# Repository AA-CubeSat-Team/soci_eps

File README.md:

# soci_eps

This is a repo for the EPS (electrical power system) subsystem of SOC-I.

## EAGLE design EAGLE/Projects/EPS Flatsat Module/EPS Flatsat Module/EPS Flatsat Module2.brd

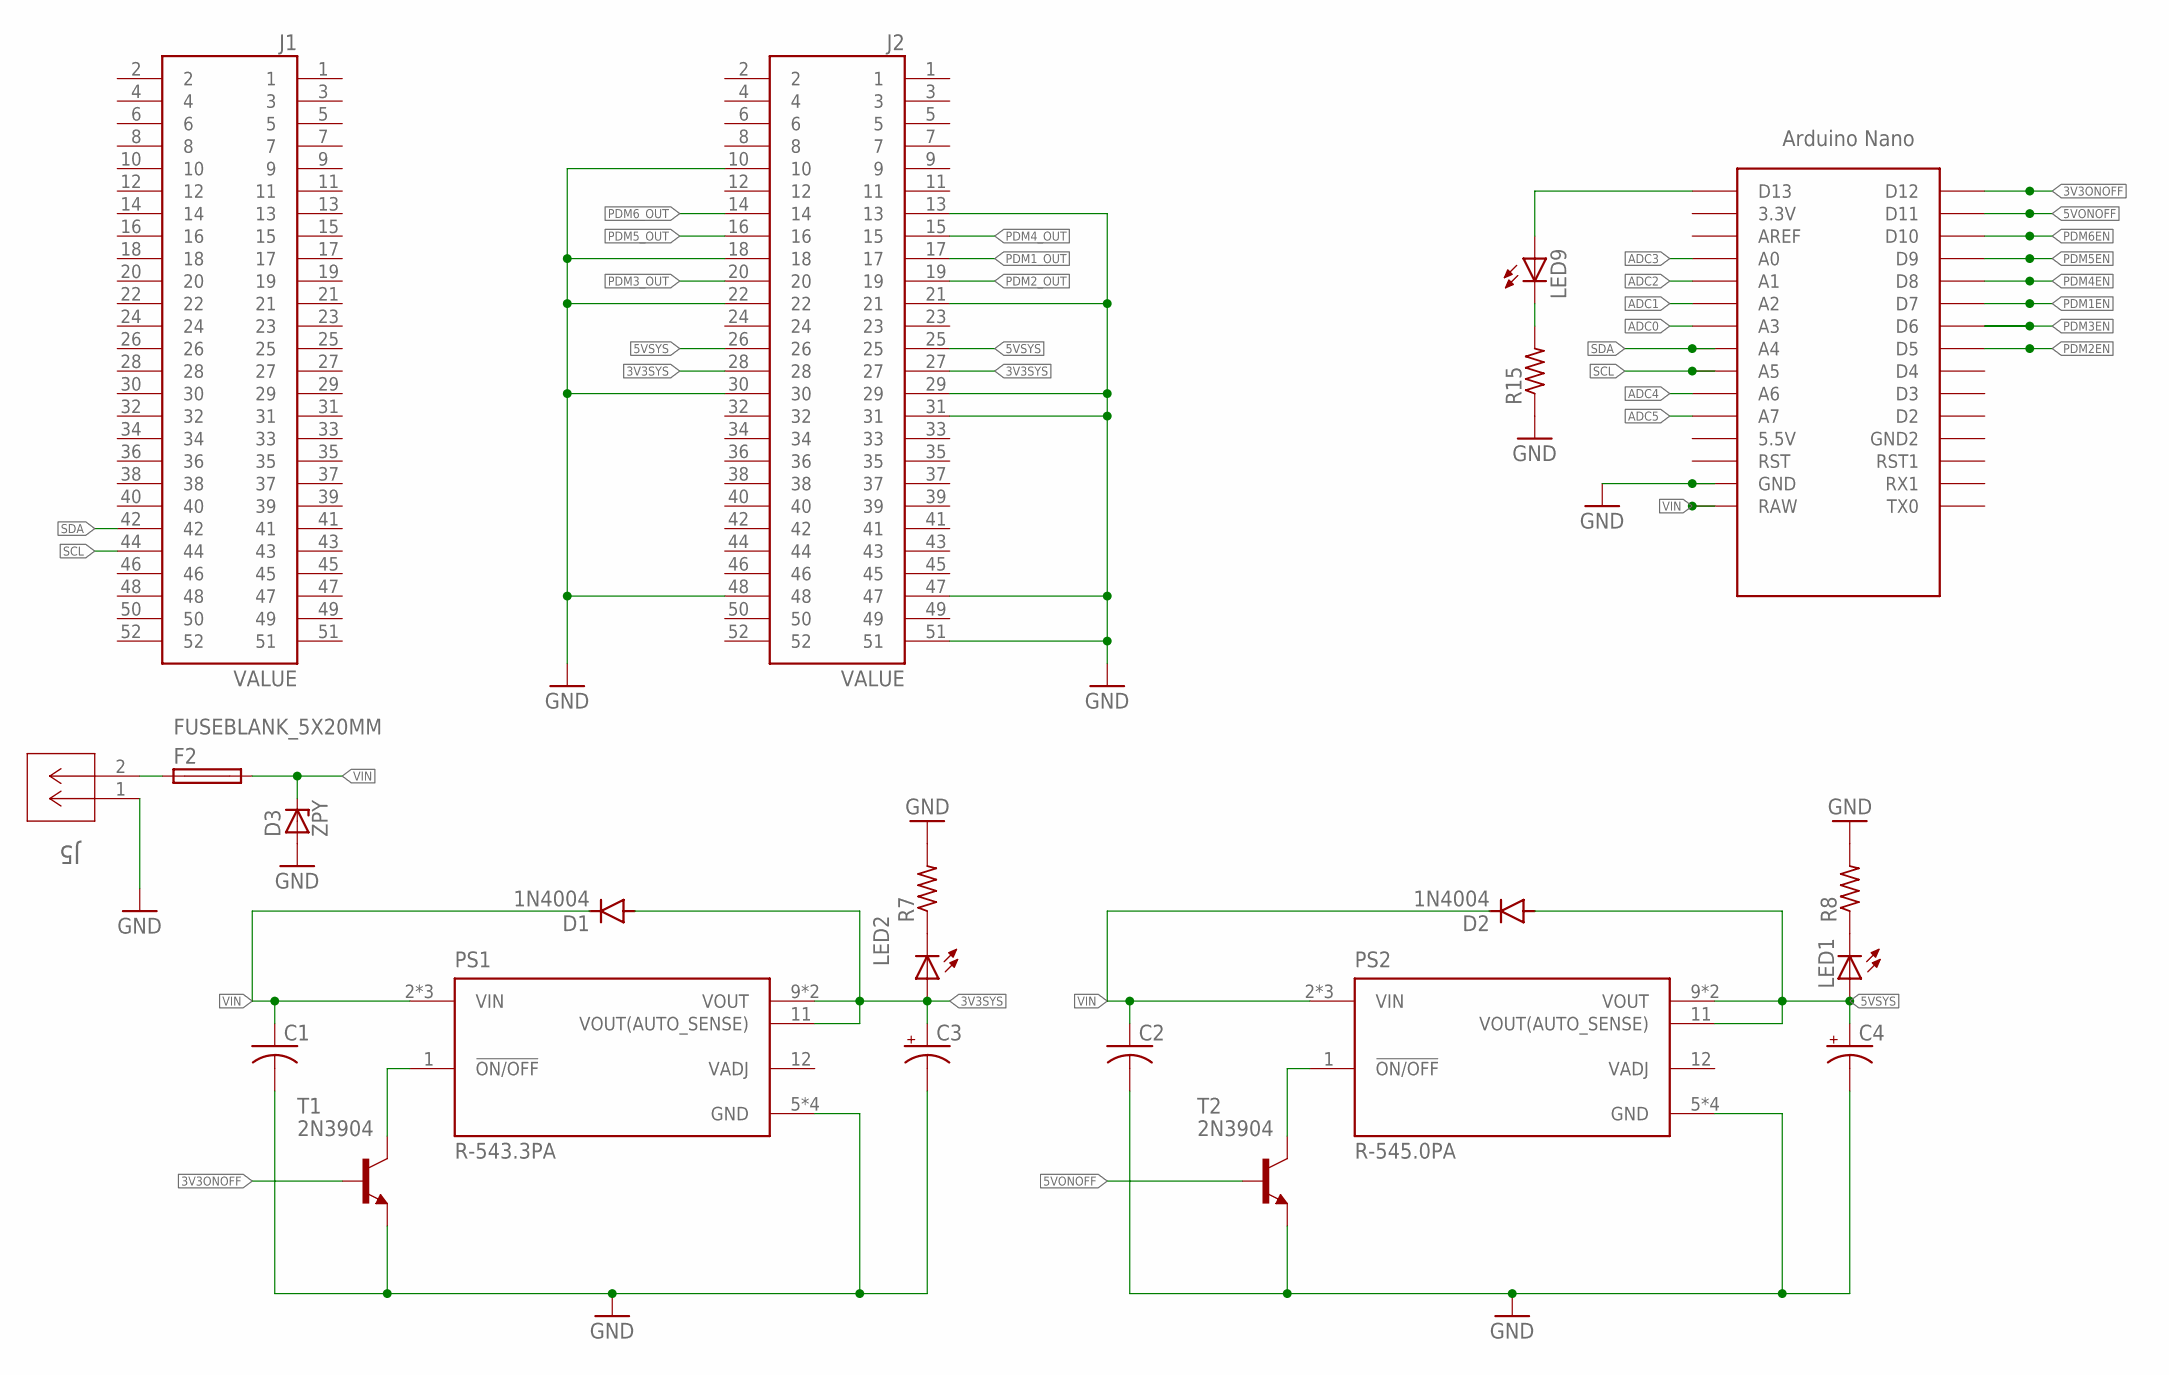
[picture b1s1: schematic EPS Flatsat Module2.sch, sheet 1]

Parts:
C1, C2: C-USC0805; C0805
C3, C4: CPOL-USE2.5-6; E2,5-6
D1, D2: 1N4004; DO41-10
D3: ZPY; DO41Z10
F2: FUSEBLANK_5X20MM; FUSE_HOLDER_5X20MM
J1, J2: ESQ-126-39-G-D; SAMTEC_ESQ-126-39-G-D
J5: 1985881; CONN_1715022_PXC
LED1, LED2: LEDCHIPLED_0805; CHIPLED_0805
LED9: LEDCHIP-LED0805; CHIP-LED0805
PS1: R-543.3PA; CONV_R-543.3PA
PS2: R-545.0PA; CONV_R-545.0PA
R7, R8, R15: R-US_R0805; R0805
T1, T2: 2N3904; TO92
U$1: NANO

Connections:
3V3ONOFF: T1.2 (B), U$1.D12
3V3SYS: C3.+, D1.A, J2.27, J2.28, LED2.A, PS1.9 (VOUT), PS1.10 (VOUT), PS1.11 (VOUT(AUTO_SENSE)); also elsewhere on the board
5VONOFF: T2.2 (B), U$1.D11
5VSYS: C4.+, D2.A, J2.25, J2.26, LED1.A, PS2.9 (VOUT), PS2.10 (VOUT), PS2.11 (VOUT(AUTO_SENSE)); also elsewhere on the board
ADC0: U$1.A3; also elsewhere on the board
ADC1: U$1.A2; also elsewhere on the board
ADC2: U$1.A1; also elsewhere on the board
ADC3: U$1.A0; also elsewhere on the board
ADC4: U$1.A6; also elsewhere on the board
ADC5: U$1.A7; also elsewhere on the board
GND: C1.2, C2.2, C3.-, C4.-, D3.A, J2.10, J2.13, J2.18, J2.21, J2.22, J2.29, J2.30, J2.31, J2.47, J2.48, J2.51, J5.1, PS1.5 (GND), PS1.6 (GND), PS1.7 (GND), PS1.8 (GND), PS2.5 (GND), PS2.6 (GND), PS2.7 (GND), PS2.8 (GND), R7.2, R8.2, R15.1, T1.3 (E), T2.3 (E), U$1.GND; also elsewhere on the board
unnamed: PS1.1 (!ON/OFF), T1.1 (C)
unnamed: PS2.1 (!ON/OFF), T2.1 (C)
unnamed: LED1.C, R8.1
unnamed: LED2.C, R7.1
unnamed: F2.1, J5.2
unnamed: LED9.A, U$1.D13
unnamed: LED9.C, R15.2
PDM1EN: U$1.D7; also elsewhere on the board
PDM1_OUT: J2.17; also elsewhere on the board
PDM2EN: U$1.D5; also elsewhere on the board
PDM2_OUT: J2.19; also elsewhere on the board
PDM3EN: U$1.D6; also elsewhere on the board
PDM3_OUT: J2.20; also elsewhere on the board
PDM4EN: U$1.D8; also elsewhere on the board
PDM4_OUT: J2.15; also elsewhere on the board
PDM5EN: U$1.D9; also elsewhere on the board
PDM5_OUT: J2.16; also elsewhere on the board
PDM6EN: U$1.D10; also elsewhere on the board
PDM6_OUT: J2.14; also elsewhere on the board
SCL: J1.44, U$1.A5
SDA: J1.42, U$1.A4
VIN: C1.1, C2.1, D1.C, D2.C, D3.C, F2.2, PS1.2 (VIN), PS1.3 (VIN), PS1.4 (VIN), PS2.2 (VIN), PS2.3 (VIN), PS2.4 (VIN), U$1.RAW

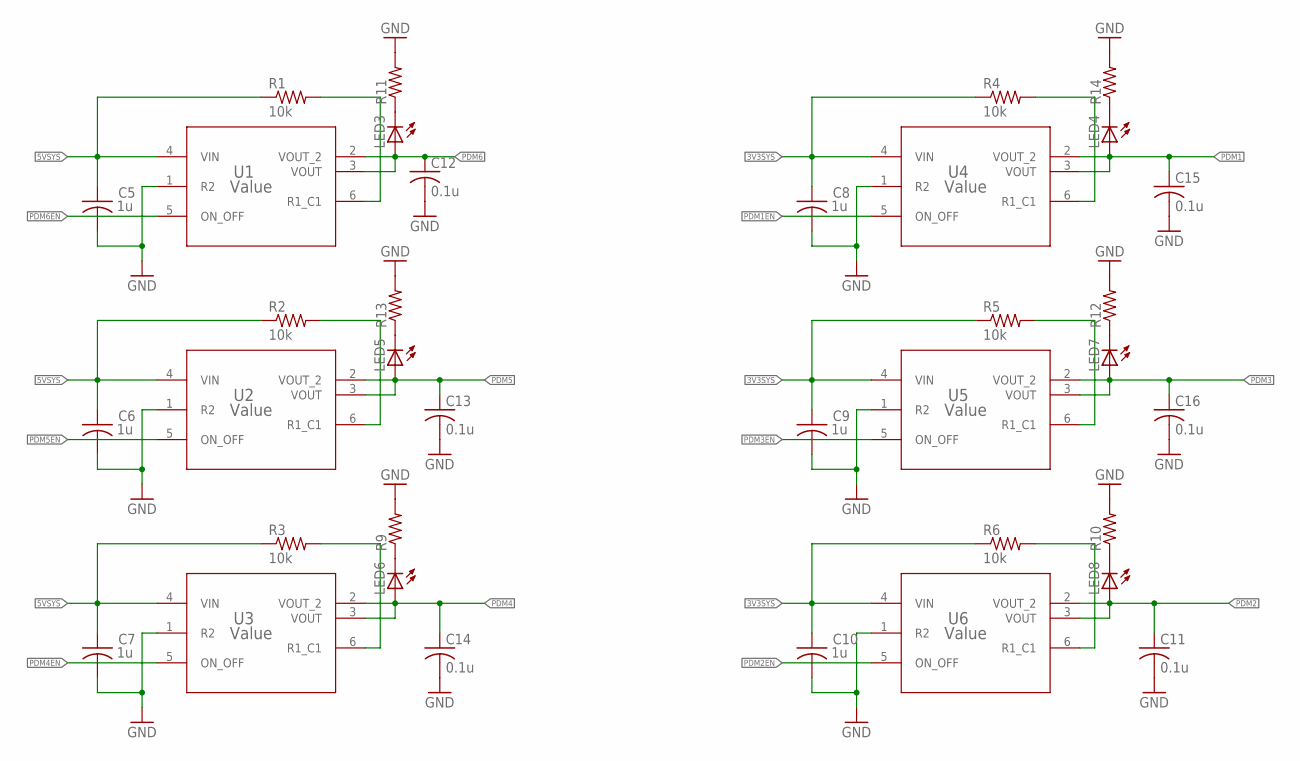
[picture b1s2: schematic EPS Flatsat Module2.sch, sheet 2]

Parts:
C5, C6, C7, C8, C9, C10: 1u; C0805
C11, C12, C13, C14, C15, C16: 0.1u; C0805
LED3, LED4, LED5, LED6, LED7, LED8: LEDCHIPLED_0805; CHIPLED_0805
R1, R2, R3, R4, R5, R6: 10k; R0805
R9, R10, R11, R12, R13, R14: R-US_R0805; R0805
U1, U2, U3, U4, U5, U6: Value; DDC0006A_N

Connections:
3V3SYS: C8.1, C9.1, C10.1, R4.1, R5.1, R6.1, U4.4 (VIN), U5.4 (VIN), U6.4 (VIN); also elsewhere on the board
5VSYS: C5.1, C6.1, C7.1, R1.1, R2.1, R3.1, U1.4 (VIN), U2.4 (VIN), U3.4 (VIN); also elsewhere on the board
GND: C5.2, C6.2, C7.2, C8.2, C9.2, C10.2, C11.2, C12.2, C13.2, C14.2, C15.2, C16.2, R9.2, R10.2, R11.2, R12.2, R13.2, R14.2, U1.1 (R2), U2.1 (R2), U3.1 (R2), U4.1 (R2), U5.1 (R2), U6.1 (R2); also elsewhere on the board
unnamed: R1.2, U1.6 (R1_C1)
unnamed: R2.2, U2.6 (R1_C1)
unnamed: R3.2, U3.6 (R1_C1)
unnamed: R4.2, U4.6 (R1_C1)
unnamed: R5.2, U5.6 (R1_C1)
unnamed: R6.2, U6.6 (R1_C1)
unnamed: LED6.C, R9.1
unnamed: LED3.C, R11.1
unnamed: LED4.C, R14.1
unnamed: LED7.C, R12.1
unnamed: LED5.C, R13.1
unnamed: LED8.C, R10.1
PDM1: C15.1, LED4.A, U4.2 (VOUT_2), U4.3 (VOUT); also elsewhere on the board
PDM1EN: U4.5 (ON_OFF); also elsewhere on the board
PDM2: C11.1, LED8.A, U6.2 (VOUT_2), U6.3 (VOUT); also elsewhere on the board
PDM2EN: U6.5 (ON_OFF); also elsewhere on the board
PDM3: C16.1, LED7.A, U5.2 (VOUT_2), U5.3 (VOUT); also elsewhere on the board
PDM3EN: U5.5 (ON_OFF); also elsewhere on the board
PDM4: C14.1, LED6.A, U3.2 (VOUT_2), U3.3 (VOUT); also elsewhere on the board
PDM4EN: U3.5 (ON_OFF); also elsewhere on the board
PDM5: C13.1, LED5.A, U2.2 (VOUT_2), U2.3 (VOUT); also elsewhere on the board
PDM5EN: U2.5 (ON_OFF); also elsewhere on the board
PDM6: C12.1, LED3.A, U1.2 (VOUT_2), U1.3 (VOUT); also elsewhere on the board
PDM6EN: U1.5 (ON_OFF); also elsewhere on the board

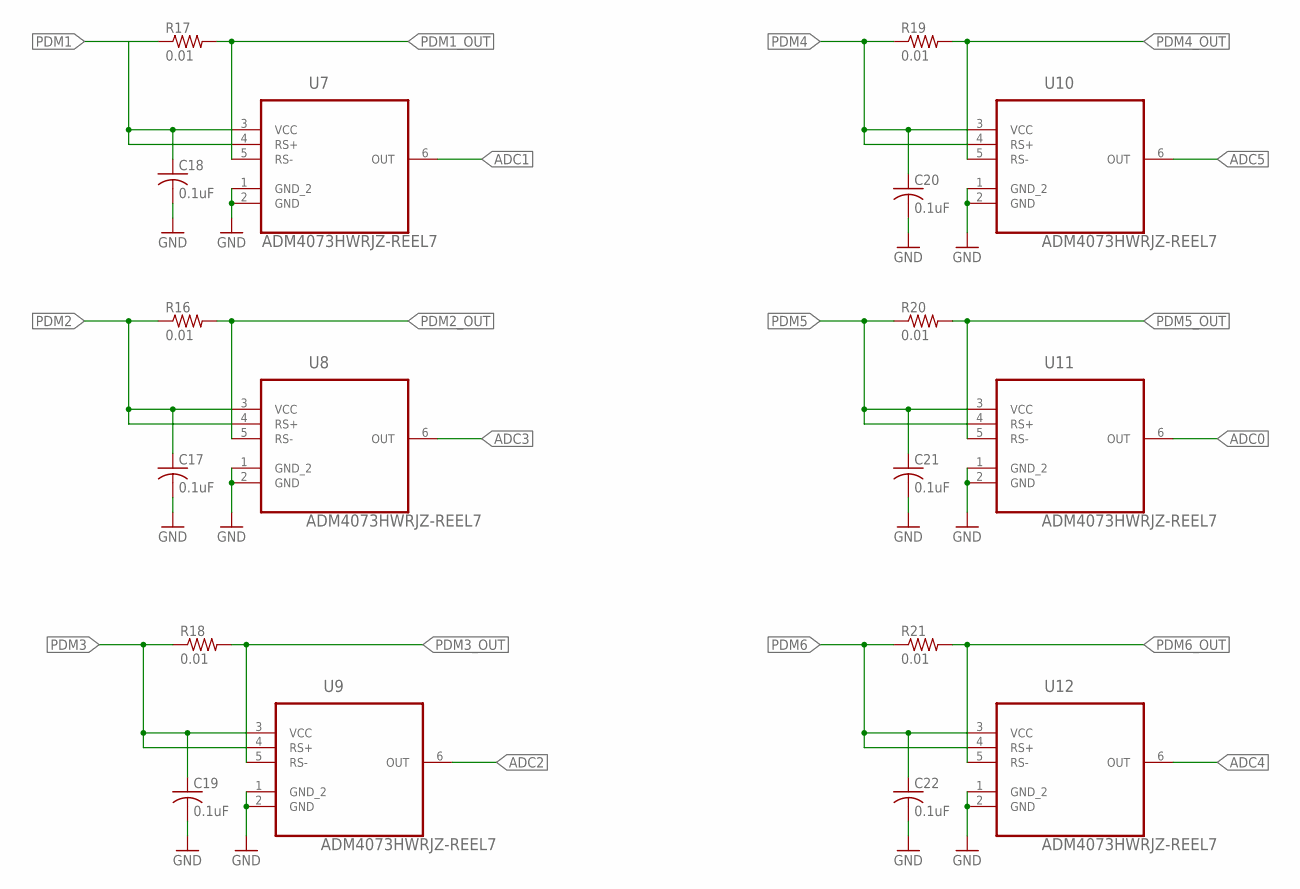
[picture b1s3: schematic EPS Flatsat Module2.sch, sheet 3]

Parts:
C17, C18, C19, C20, C21, C22: 0.1uF; C0805
R16, R17, R18, R19, R20, R21: 0.01; R2512
U7, U8, U9, U10, U11, U12: ADM4073HWRJZ-REEL7; SOT95P290X145-6N

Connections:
ADC0: U11.6 (OUT); also elsewhere on the board
ADC1: U7.6 (OUT); also elsewhere on the board
ADC2: U9.6 (OUT); also elsewhere on the board
ADC3: U8.6 (OUT); also elsewhere on the board
ADC4: U12.6 (OUT); also elsewhere on the board
ADC5: U10.6 (OUT); also elsewhere on the board
GND: C17.2, C18.2, C19.2, C20.2, C21.2, C22.2, U7.1 (GND_2), U7.2 (GND), U8.1 (GND_2), U8.2 (GND), U9.1 (GND_2), U9.2 (GND), U10.1 (GND_2), U10.2 (GND), U11.1 (GND_2), U11.2 (GND), U12.1 (GND_2), U12.2 (GND); also elsewhere on the board
PDM1: C18.1, R17.1, U7.3 (VCC), U7.4 (RS+); also elsewhere on the board
PDM1_OUT: R17.2, U7.5 (RS-); also elsewhere on the board
PDM2: C17.1, R16.1, U8.3 (VCC), U8.4 (RS+); also elsewhere on the board
PDM2_OUT: R16.2, U8.5 (RS-); also elsewhere on the board
PDM3: C19.1, R18.1, U9.3 (VCC), U9.4 (RS+); also elsewhere on the board
PDM3_OUT: R18.2, U9.5 (RS-); also elsewhere on the board
PDM4: C20.1, R19.1, U10.3 (VCC), U10.4 (RS+); also elsewhere on the board
PDM4_OUT: R19.2, U10.5 (RS-); also elsewhere on the board
PDM5: C21.1, R20.1, U11.3 (VCC), U11.4 (RS+); also elsewhere on the board
PDM5_OUT: R20.2, U11.5 (RS-); also elsewhere on the board
PDM6: C22.1, R21.1, U12.3 (VCC), U12.4 (RS+); also elsewhere on the board
PDM6_OUT: R21.2, U12.5 (RS-); also elsewhere on the board

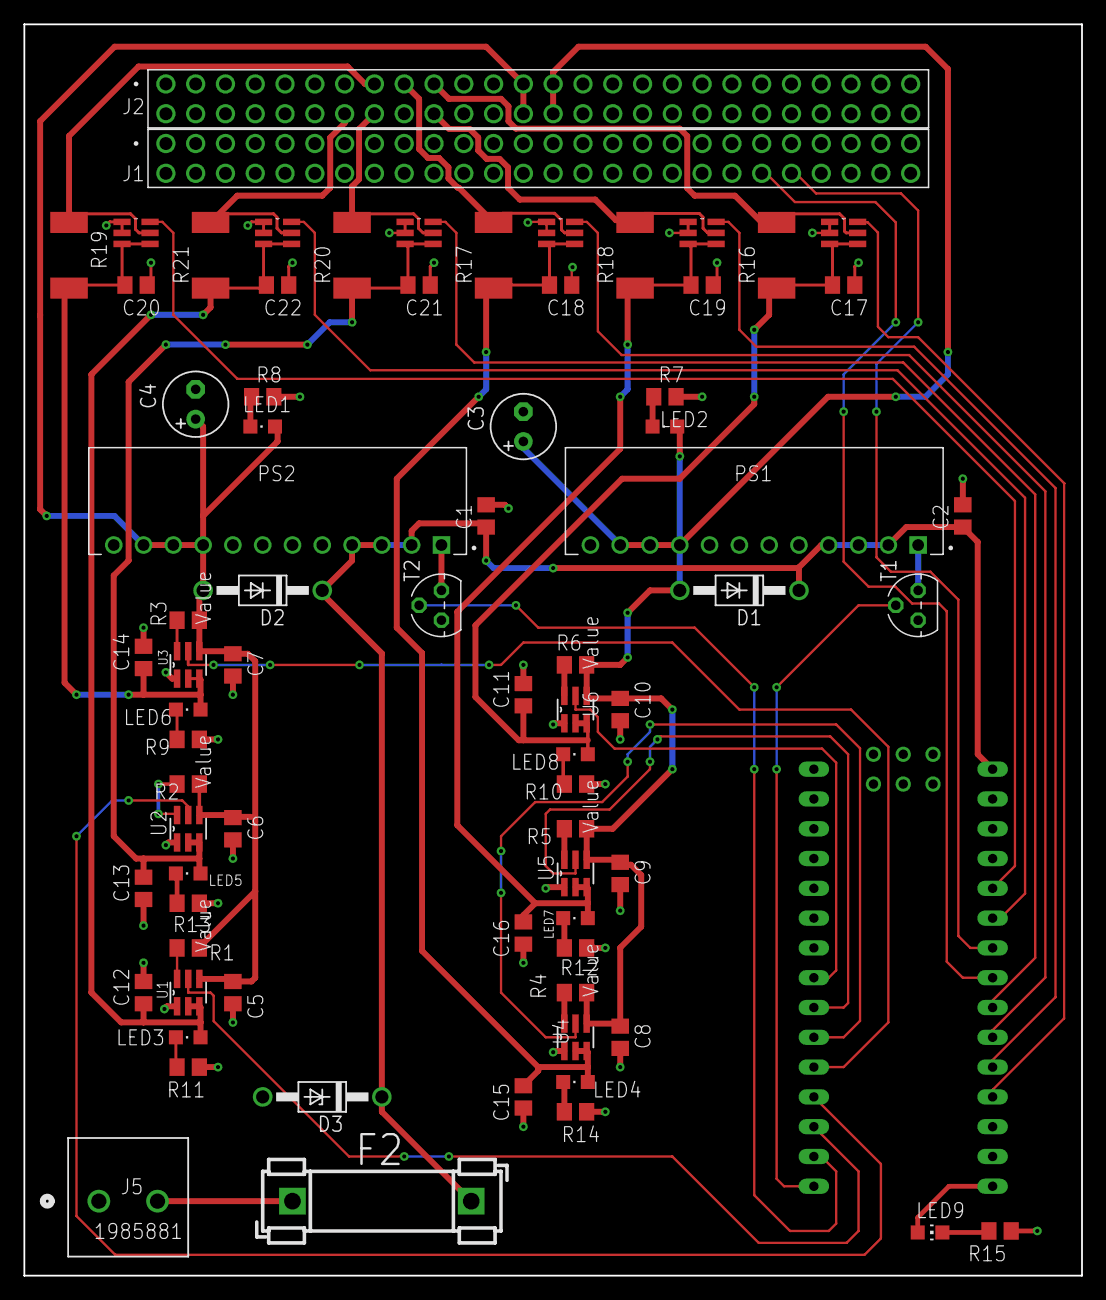
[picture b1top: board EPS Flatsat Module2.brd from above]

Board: 2 copper layers, 90.2 x 106.7 mm, 76 parts (0 on the bottom side), 51 nets.

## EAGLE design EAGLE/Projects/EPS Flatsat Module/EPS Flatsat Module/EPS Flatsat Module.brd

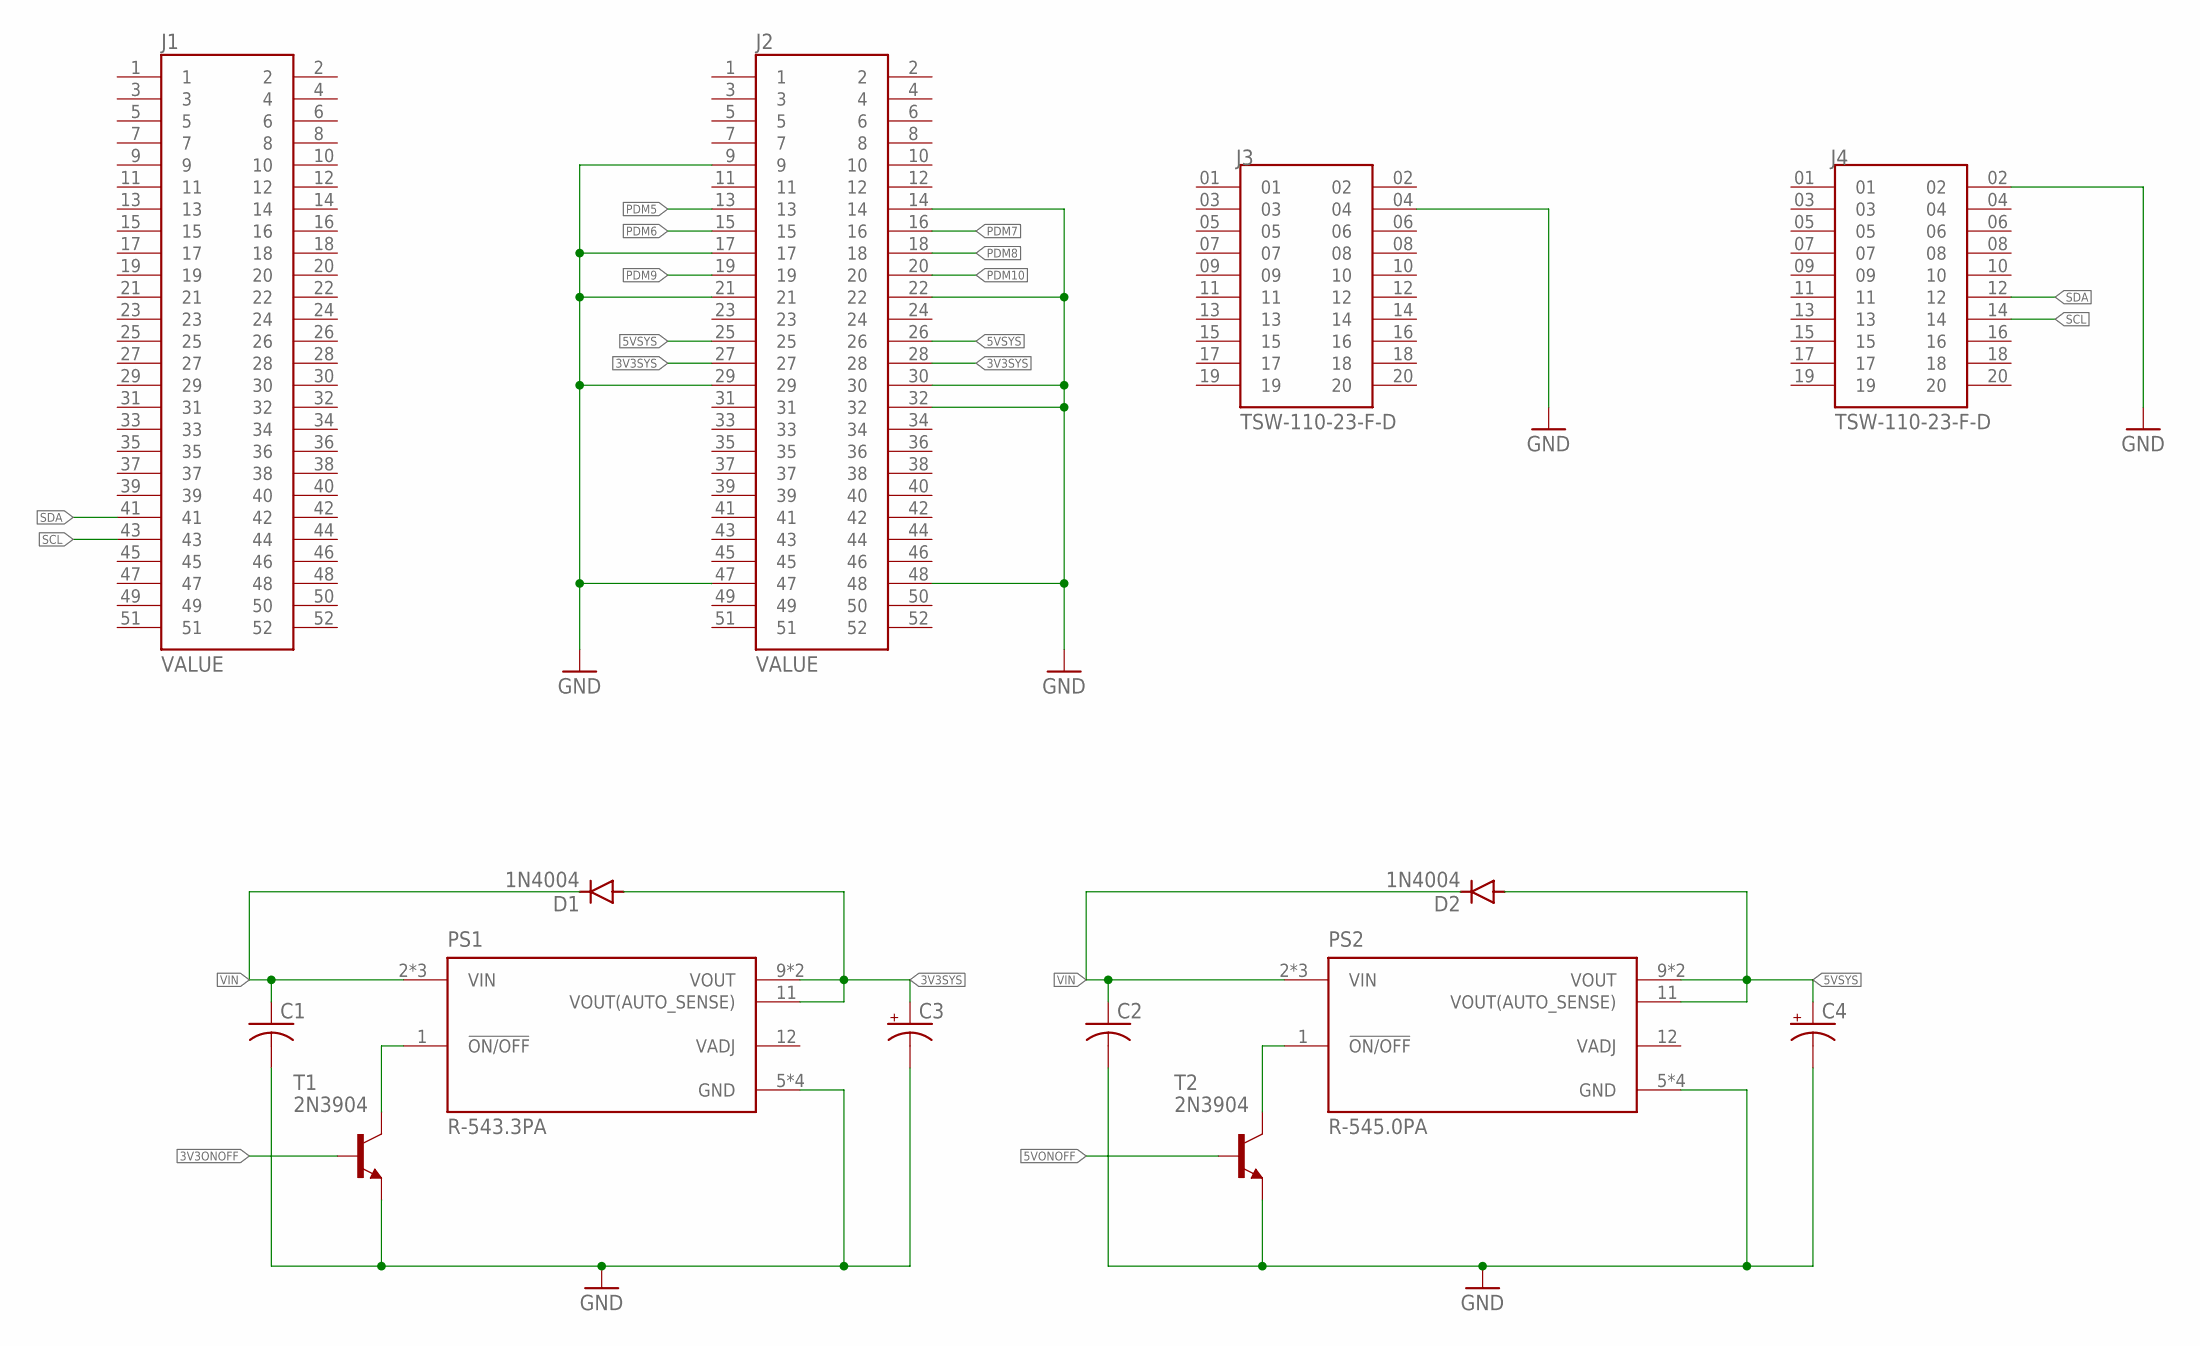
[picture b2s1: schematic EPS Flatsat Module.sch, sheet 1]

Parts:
C1, C2: C-USC0805; C0805
C3, C4: CPOL-USE2.5-6; E2,5-6
D1, D2: 1N4004; DO41-10
J1, J2: ESQ-126-39-G-D; SAMTEC_ESQ-126-39-G-D
J3, J4: TSW-110-23-F-D; SAMTEC_TSW-110-23-F-D
PS1: R-543.3PA; CONV_R-543.3PA
PS2: R-545.0PA; CONV_R-545.0PA
T1, T2: 2N3904; TO92

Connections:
3V3ONOFF: T1.2 (B)
3V3SYS: C3.+, D1.A, J2.27, J2.28, PS1.9 (VOUT), PS1.10 (VOUT), PS1.11 (VOUT(AUTO_SENSE)); also elsewhere on the board
5VONOFF: T2.2 (B)
5VSYS: C4.+, D2.A, J2.25, J2.26, PS2.9 (VOUT), PS2.10 (VOUT), PS2.11 (VOUT(AUTO_SENSE)); also elsewhere on the board
GND: C1.2, C2.2, C3.-, C4.-, J2.9, J2.14, J2.17, J2.21, J2.22, J2.29, J2.30, J2.32, J2.47, J2.48, J3.04, J4.02, PS1.5 (GND), PS1.6 (GND), PS1.7 (GND), PS1.8 (GND), PS2.5 (GND), PS2.6 (GND), PS2.7 (GND), PS2.8 (GND), T1.3 (E), T2.3 (E); also elsewhere on the board
unnamed: PS1.1 (!ON/OFF), T1.1 (C)
unnamed: PS2.1 (!ON/OFF), T2.1 (C)
PDM5: J2.13; also elsewhere on the board
PDM6: J2.15; also elsewhere on the board
PDM7: J2.16; also elsewhere on the board
PDM8: J2.18; also elsewhere on the board
PDM9: J2.19; also elsewhere on the board
PDM10: J2.20; also elsewhere on the board
SCL: J1.43, J4.14
SDA: J1.41, J4.12
VIN: C1.1, C2.1, D1.C, D2.C, PS1.2 (VIN), PS1.3 (VIN), PS1.4 (VIN), PS2.2 (VIN), PS2.3 (VIN), PS2.4 (VIN)

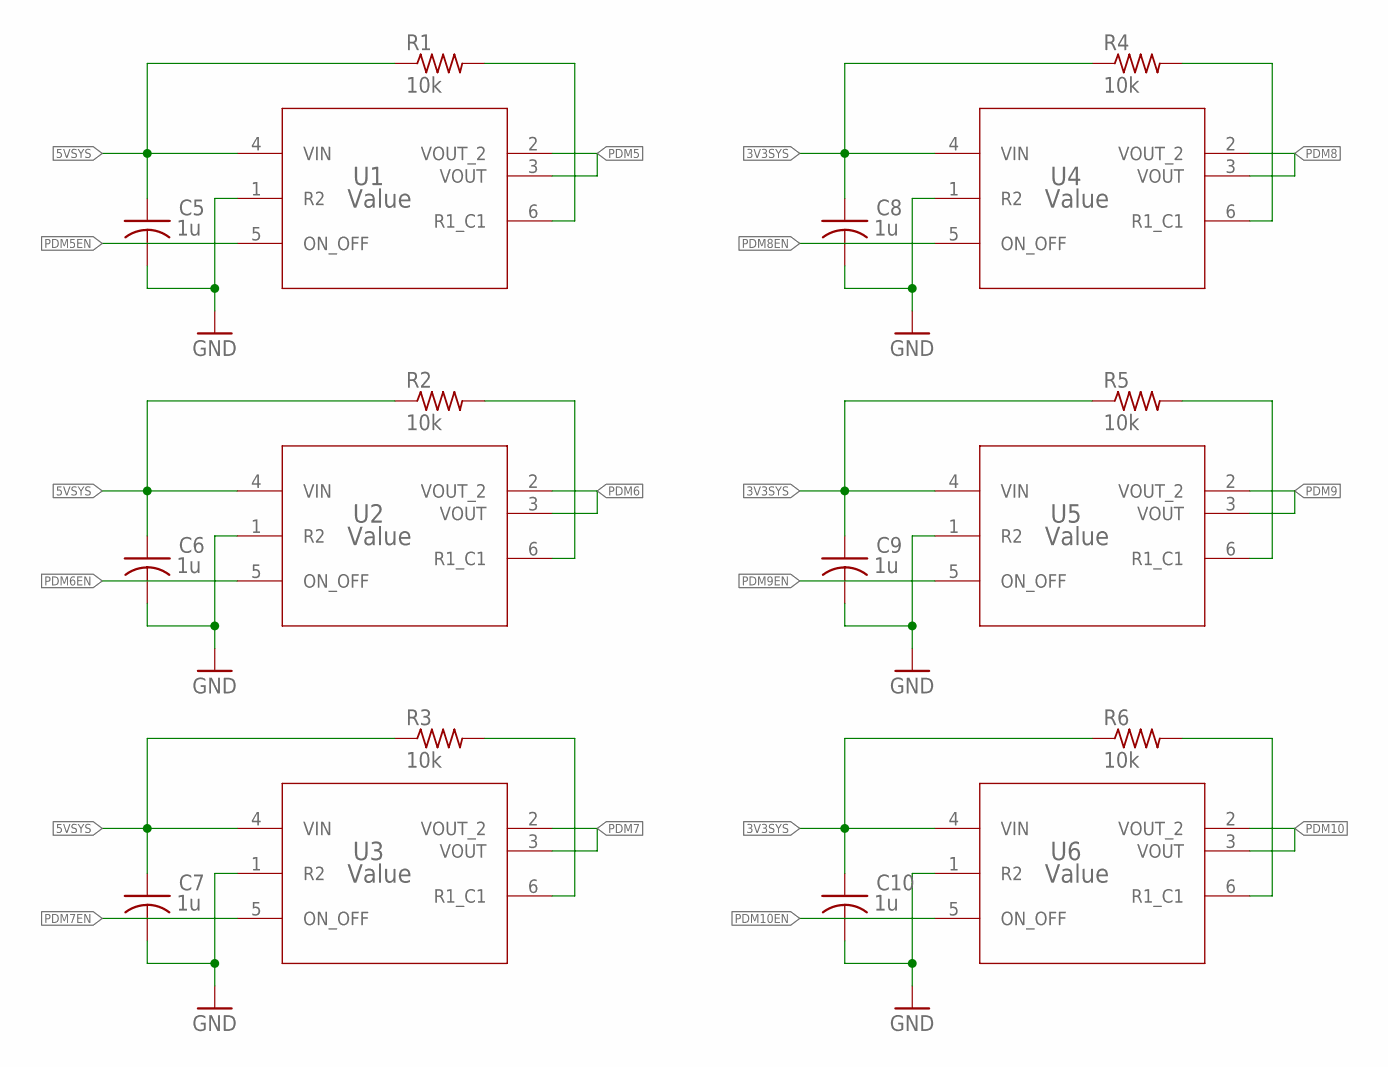
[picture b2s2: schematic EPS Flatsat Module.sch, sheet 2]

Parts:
C5, C6, C7, C8, C9, C10: 1u; C0805
R1, R2, R3, R4, R5, R6: 10k; R0805
U1, U2, U3, U4, U5, U6: Value; DDC0006A_N

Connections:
3V3SYS: C8.1, C9.1, C10.1, R4.1, R5.1, R6.1, U4.4 (VIN), U5.4 (VIN), U6.4 (VIN); also elsewhere on the board
5VSYS: C5.1, C6.1, C7.1, R1.1, R2.1, R3.1, U1.4 (VIN), U2.4 (VIN), U3.4 (VIN); also elsewhere on the board
GND: C5.2, C6.2, C7.2, C8.2, C9.2, C10.2, U1.1 (R2), U2.1 (R2), U3.1 (R2), U4.1 (R2), U5.1 (R2), U6.1 (R2); also elsewhere on the board
unnamed: R1.2, U1.6 (R1_C1)
unnamed: R2.2, U2.6 (R1_C1)
unnamed: R3.2, U3.6 (R1_C1)
unnamed: R4.2, U4.6 (R1_C1)
unnamed: R5.2, U5.6 (R1_C1)
unnamed: R6.2, U6.6 (R1_C1)
PDM5: U1.2 (VOUT_2), U1.3 (VOUT); also elsewhere on the board
PDM5EN: U1.5 (ON_OFF)
PDM6: U2.2 (VOUT_2), U2.3 (VOUT); also elsewhere on the board
PDM6EN: U2.5 (ON_OFF)
PDM7: U3.2 (VOUT_2), U3.3 (VOUT); also elsewhere on the board
PDM7EN: U3.5 (ON_OFF)
PDM8: U4.2 (VOUT_2), U4.3 (VOUT); also elsewhere on the board
PDM8EN: U4.5 (ON_OFF)
PDM9: U5.2 (VOUT_2), U5.3 (VOUT); also elsewhere on the board
PDM9EN: U5.5 (ON_OFF)
PDM10: U6.2 (VOUT_2), U6.3 (VOUT); also elsewhere on the board
PDM10EN: U6.5 (ON_OFF)

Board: 2 copper layers, 32 parts (0 on the bottom side), 20 nets, no tracks yet.

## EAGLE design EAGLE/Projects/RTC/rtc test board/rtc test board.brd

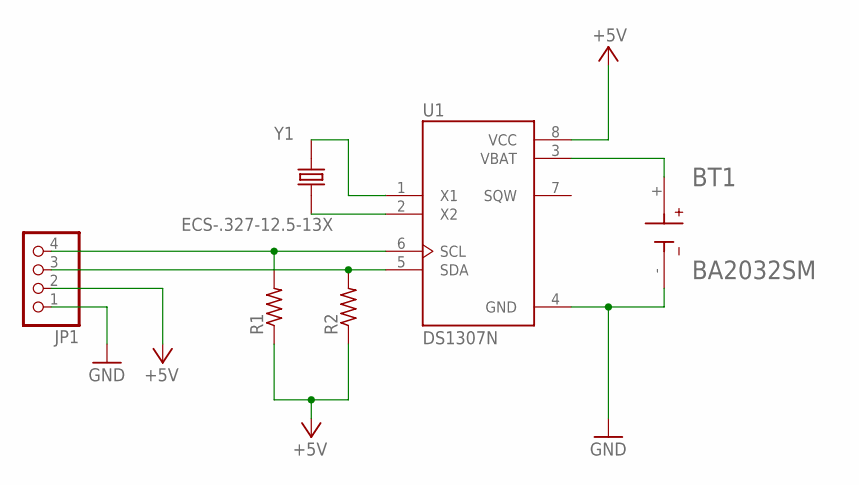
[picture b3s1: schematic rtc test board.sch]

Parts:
BT1: BA2032SM; BAT_BA2032SM
JP1: PINHD-1X4; 1X04
R1, R2: R-US_R0805; R0805
U1: DS1307N; DIP762W47P254L991H457Q8
Y1: ECS-.327-12.5-13X; XTAL_ECS-.327-12.5-13X

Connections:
+5V: JP1.2, R1.1, R2.1, U1.8 (VCC)
GND: BT1.-, JP1.1, U1.4 (GND)
unnamed: U1.2 (X2), Y1.2
unnamed: U1.1 (X1), Y1.1
unnamed: JP1.4, R1.2, U1.6 (SCL)
unnamed: JP1.3, R2.2, U1.5 (SDA)
unnamed: BT1.+, U1.3 (VBAT)

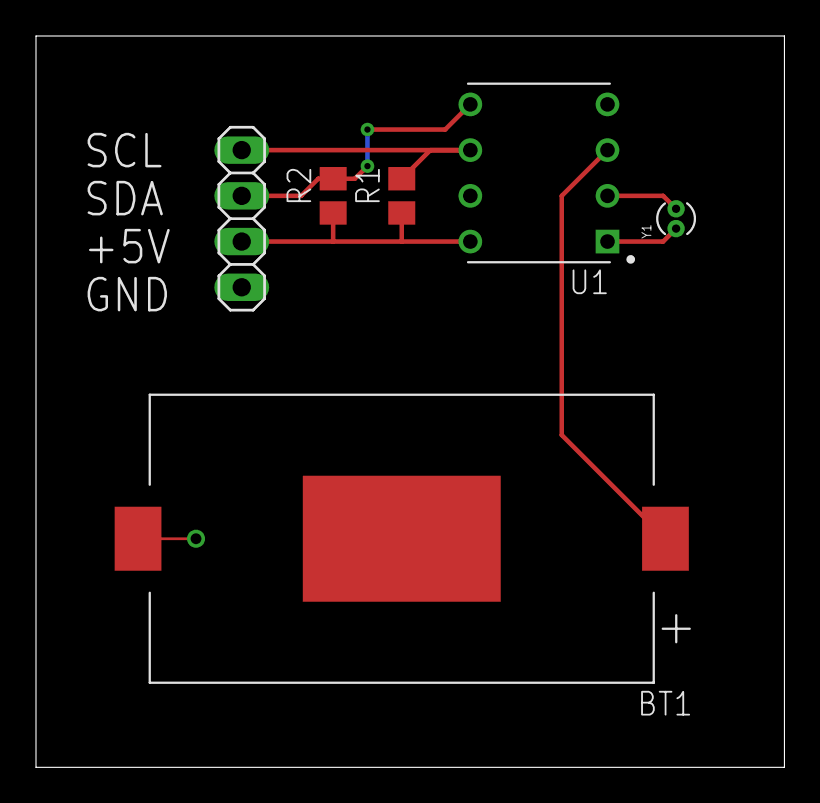
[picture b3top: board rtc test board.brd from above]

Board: 2 copper layers, 41.6 x 40.6 mm, 6 parts (0 on the bottom side), 7 nets.

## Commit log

2020-04-15 Added directory for eagle projects and libraries. Added RTC project and associated libraries.
2020-04-15 Added .gitignore for C project in CCS
2020-04-15 Added CCS project with test code for RTC circuit, tested using MSP430
2020-04-15 Updated .gitignore
2020-04-15 temp removed RTC dir
2020-04-15 added RTC directory, with RTC test code
2020-04-28 Added gnc submodule
2020-04-28 Updated gnc submodule to branch dev_cole
2020-04-28 Added power simulation
2020-04-28 Added power sim
2020-05-22 Created EAGLE project for flatsat module
2020-06-23 small updates to power sim
2020-06-23 Updates to flatsat module. Added MSP430 headers, DCDC converters, and some power switches to schematic. Did some placement on the board layout.
2020-06-23 Created flight software directory, which includes soci_cdh_drivers as a git submodule. Started on a template for the drivers that the OBC will need to communicate with EPS via i2c
2020-07-07 small updates to power sim, and added script to compute power after running sim
2020-07-07 Updated submodules
2020-07-07 Updated power model. Switched to using most recent dev branch of soci-gnc
2020-07-09 Updated script to compute power budget
2020-07-17 Updated power module. Added flags in matlab script to enable subsystems, and updated analyze script to run through multiple simulations
2020-07-30 created batt voltage function
2020-08-02 IPCM12V -> VPCM3V3 added
2020-08-09 8/8 changes
2020-08-11 8/11
2020-08-25 Updated flatsat module schematic/board
2020-08-30 added 8/30
2020-09-03 updated 9/3
2020-09-03 Updated fuse, changed MSP header spacing, small layout edits
2020-09-08 test
2020-09-09 updated 9/9
2020-09-27 updated 9/27
2020-10-15 Small updates to get power sim working. Updated script to compute average power of each subsystem and save them to a file
2020-10-26 Added TVS diode, changed microcontroller to Arduino Nano, redid traces
2020-10-28 Update to board layout
2020-11-27 updated 11/26
2020-12-07 added 12/6/20
2020-12-30 added 12/30/20
2021-01-23 added 1/23/21
2021-01-25 added 1/24/21
2021-01-31 added 1/30/21
2021-01-31 test 1/31/21
2021-02-20 added 2/20/21
2021-02-21 reorganized 2/20
2021-02-21 added telemetry (still incomplete)
2021-02-27 rough telemetry finished
2021-02-27 telemetry updated needs to be checked
2021-03-02 Upload flatsat sim software and test software
2021-03-04 3/4 completed telemetry (untested)
2021-03-04 telemetry needs check and suggested corrections are fixed
2021-03-04 old telemetry
2021-03-08 changes in description
    adc_count is returned in bat module stat and power mod stat. Old telemetry is moved over to dif file (inside old eps file)
2021-03-10 fixed header and fixed eps
2021-03-10 merged version w cdh
2021-03-14 debug 3/13
2021-03-23 Add current sense fucntionality
2021-04-06 fixed twosComp
2021-04-20 Updated EPS sim 4/20/2021
2021-05-11 Added current sensing
2021-05-12 Debug flatsat simulation software
2021-05-13 Update documentation in EPS_Listener
2021-05-19 Create controller for Flatsat EPS arduino
2021-05-19 Add functionality to EPS_Controller
2021-06-01 Adapt testers for testing DHV hardware

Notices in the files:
parts and their libraries:
COPYRIGHT: Copyright (C) 2018 Accelerated Designs. All rights reserved
